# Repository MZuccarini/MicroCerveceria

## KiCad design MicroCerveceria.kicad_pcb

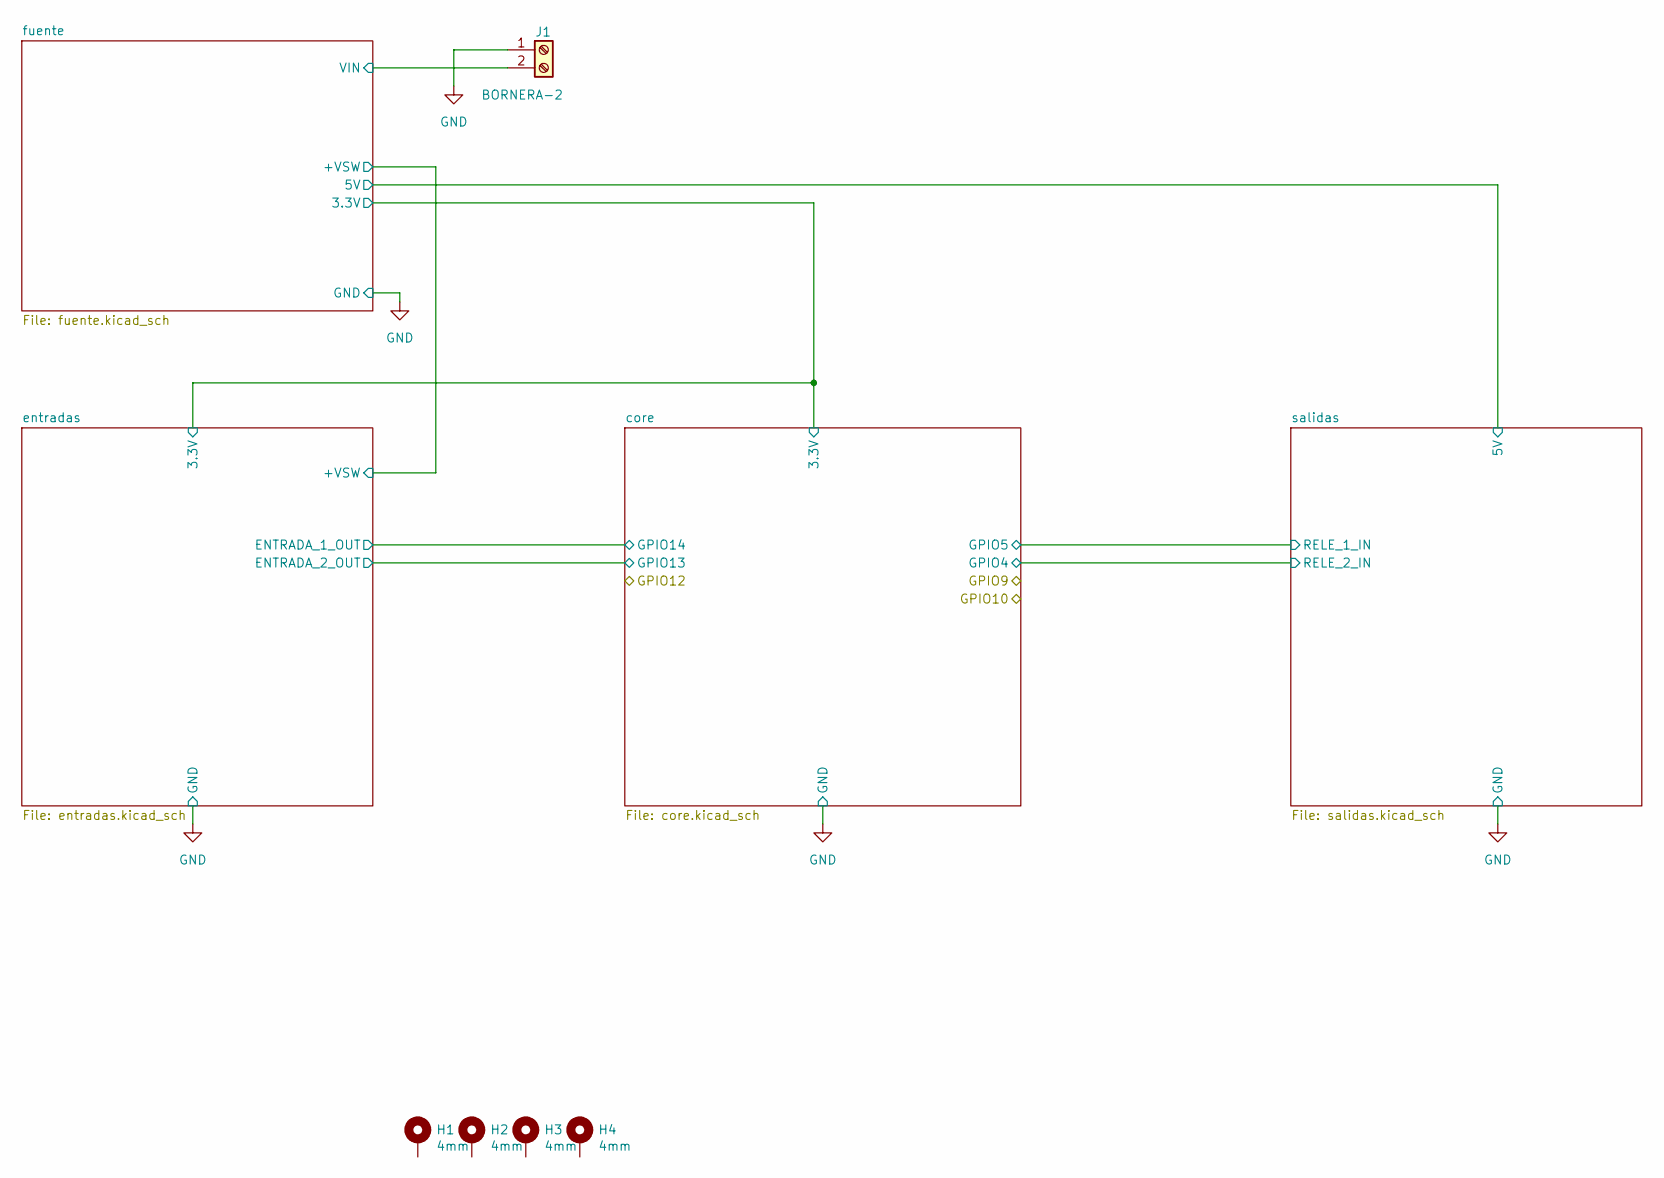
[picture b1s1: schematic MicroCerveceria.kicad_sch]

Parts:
H1, H2, H3, H4: 4mm; MountingHole_4mm_Pad
J1: BORNERA-2; TerminalBlock_Phoenix_MKDS-1,5-2-5.08_1x02_P5.08mm_Horizont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

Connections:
/fuente/VIN: J1.2; also elsewhere on the board
GND: J1.1; also elsewhere on the board

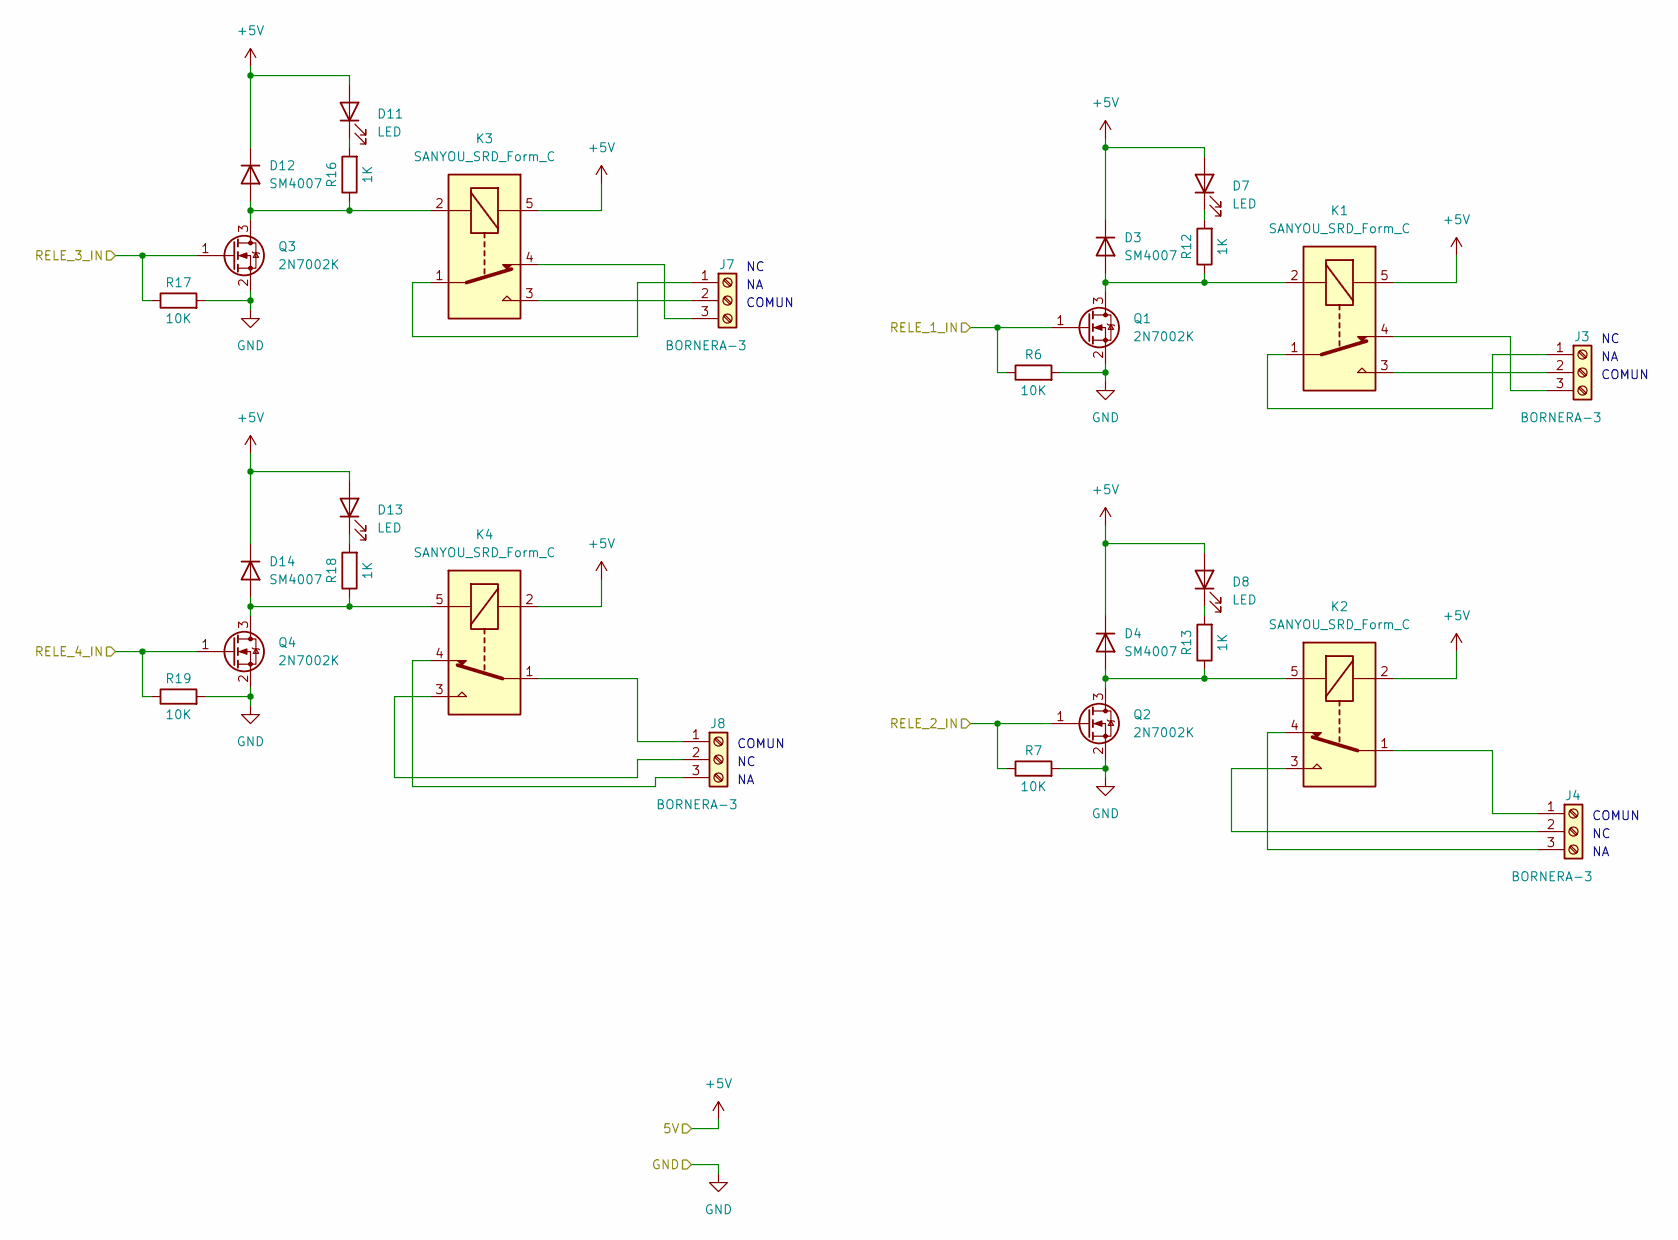
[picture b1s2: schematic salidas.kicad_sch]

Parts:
D3, D4, D12, D14: SM4007; D_SMA_Handsoldering
D7, D8, D11, D13: LED; LED_0805_2012Metric_Pad1.15x1.40mm_HandSolder
J3, J4, J7, J8: BORNERA-3; TerminalBlock_Phoenix_MKDS-1,5-3-5.08_1x03_P5.08mm_Horizont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
K1, K2, K3, K4: SANYOU_SRD_Form_C; Relay_SPDT_SANYOU_SRD_Series_Form_C
Q1, Q2, Q3, Q4: 2N7002K; SOT-23_Handsoldering
R6, R7, R17, R19: 10K; R_0805_2012Metric_Pad1.20x1.40mm_HandSolder
R12, R13, R16, R18: 1K; R_0805_2012Metric_Pad1.20x1.40mm_HandSolder

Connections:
+5V: D3.1 (K), D4.1 (K), D7.2 (A), D8.2 (A), D11.2 (A), D12.1 (K), D13.2 (A), D14.1 (K), K1.5, K2.2, K3.5, K4.2; also elsewhere on the board
/core/GPIO4: Q3.1 (G), R17.1; also elsewhere on the board
/core/GPIO5: Q4.1 (G), R19.1; also elsewhere on the board
/core/GPIO9: Q1.1 (G), R6.1; also elsewhere on the board
/core/GPIO10: Q2.1 (G), R7.1; also elsewhere on the board
GND: Q1.2 (S), Q2.2 (S), Q3.2 (S), Q4.2 (S), R6.2, R7.2, R17.2, R19.2; also elsewhere on the board
unnamed: D3.2 (A), K1.2, Q1.3 (D), R12.1
unnamed: D4.2 (A), K2.5, Q2.3 (D), R13.1
unnamed: D7.1 (K), R12.2
unnamed: D8.1 (K), R13.2
unnamed: D11.1 (K), R16.2
unnamed: D12.2 (A), K3.2, Q3.3 (D), R16.1
unnamed: D13.1 (K), R18.2
unnamed: D14.2 (A), K4.5, Q4.3 (D), R18.1
unnamed: J3.1, K1.1
unnamed: J3.2, K1.3
unnamed: J3.3, K1.4
unnamed: J4.1, K2.1
unnamed: J4.2, K2.3
unnamed: J4.3, K2.4
unnamed: J7.1, K3.1
unnamed: J7.2, K3.3
unnamed: J7.3, K3.4
unnamed: J8.1, K4.1
unnamed: J8.2, K4.3
unnamed: J8.3, K4.4

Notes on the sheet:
COMUN

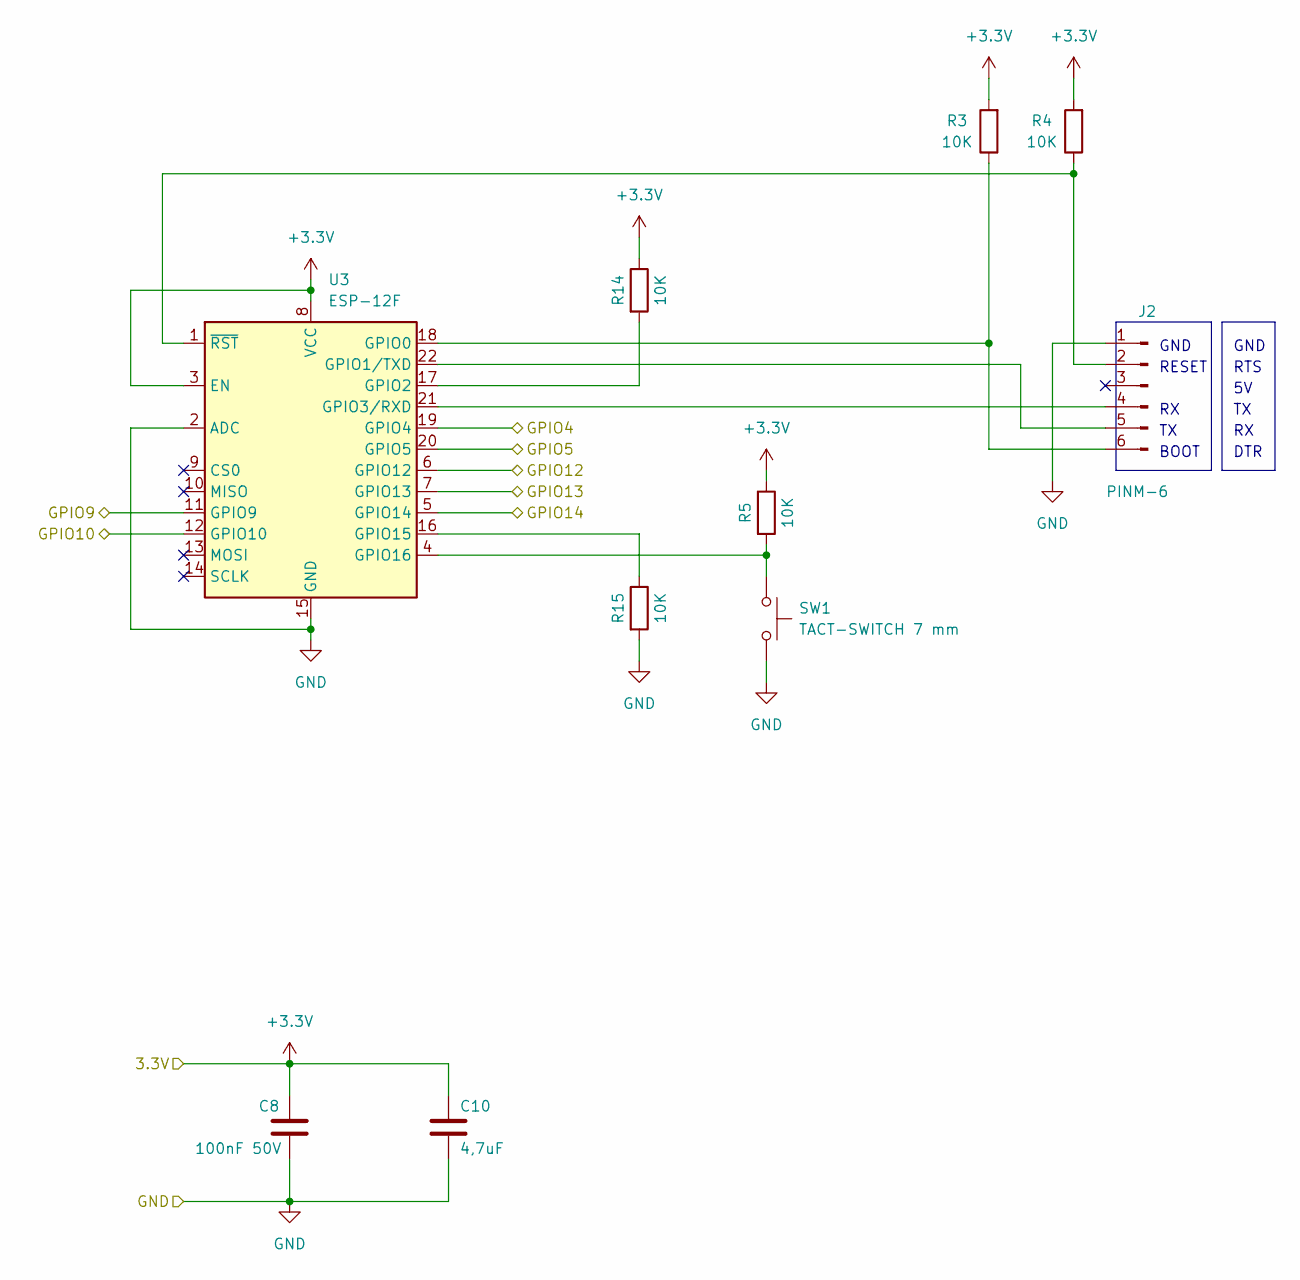
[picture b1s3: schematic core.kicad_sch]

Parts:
C8: 100nF 50V; C_0805_2012Metric_Pad1.18x1.45mm_HandSolder; DigiKey 1276-1007-2-ND
C10: 4,7uF; C_0805_2012Metric_Pad1.18x1.45mm_HandSolder
J2: PINM-6; PinHeader_1x06_P2.54mm_Vertical
R3, R4, R5, R14, R15: 10K; R_0805_2012Metric_Pad1.20x1.40mm_HandSolder
SW1: TACT-SWITCH 7 mm; SW_Tactile_SPST_Angled_PTS645Vx39-2LFS
U3: ESP-12F; ESP-12E

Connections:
+3V3: C8.1, C10.1, R3.2, R4.2, R5.1, R14.1, U3.3 (EN), U3.8 (VCC); also elsewhere on the board
/core/GPIO4: U3.19 (GPIO4); also elsewhere on the board
/core/GPIO5: U3.20 (GPIO5); also elsewhere on the board
/core/GPIO9: U3.11 (GPIO9); also elsewhere on the board
/core/GPIO10: U3.12 (GPIO10); also elsewhere on the board
/core/GPIO12: U3.6 (GPIO12); also elsewhere on the board
/core/GPIO13: U3.7 (GPIO13); also elsewhere on the board
/core/GPIO14: U3.5 (GPIO14); also elsewhere on the board
GND: C8.2, C10.2, J2.1, R15.2, SW1.1, U3.2 (ADC), U3.15 (GND); also elsewhere on the board
unnamed: J2.2, R4.1, U3.1 (~RST)
unnamed: J2.4, U3.21 (GPIO3/RXD)
unnamed: J2.5, U3.22 (GPIO1/TXD)
unnamed: J2.6, R3.1, U3.18 (GPIO0)
unnamed: R14.2, U3.17 (GPIO2)
unnamed: R15.1, U3.16 (GPIO15)
unnamed: R5.2, SW1.2, U3.4 (GPIO16)

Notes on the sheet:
GND
BOOT
RESET
RTS
DTR

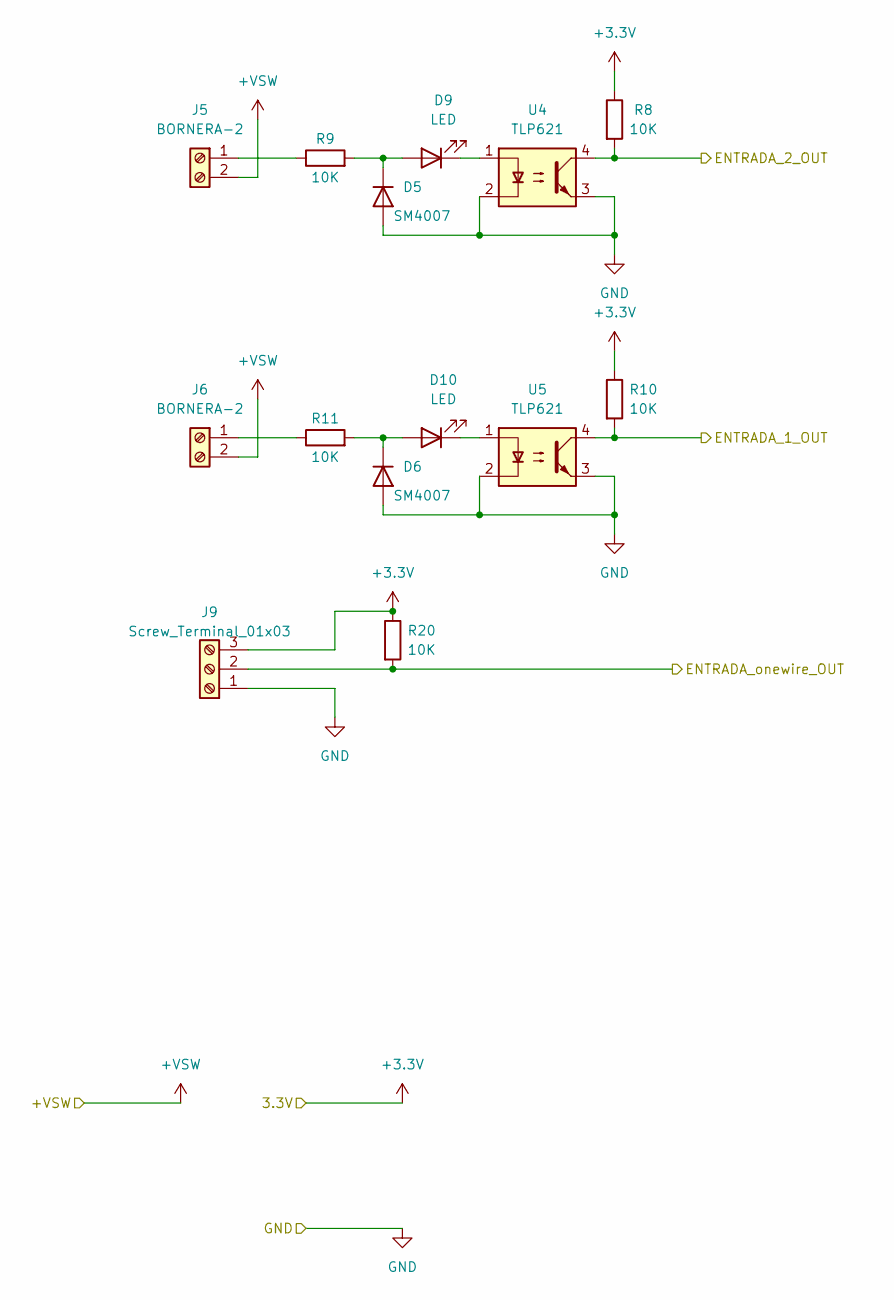
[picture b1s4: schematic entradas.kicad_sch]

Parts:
D5, D6: SM4007; D_SMA_Handsoldering
D9, D10: LED; LED_0805_2012Metric_Pad1.15x1.40mm_HandSolder
J5, J6: BORNERA-2; TerminalBlock_Phoenix_MKDS-1,5-2-5.08_1x02_P5.08mm_Horizont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
J9: Screw_Terminal_01x03; TerminalBlock_Phoenix_MKDS-1,5-3-5.08_1x03_P5.08mm_Horizont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
R8, R9, R10, R11, R20: 10K; R_0805_2012Metric_Pad1.20x1.40mm_HandSolder
U4, U5: TLP621; DIP-4_W7.62mm

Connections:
+3V3: J9.3, R8.1, R10.1, R20.1; also elsewhere on the board
+VSW: J5.2, J6.2; also elsewhere on the board
/core/GPIO12: J9.2, R20.2; also elsewhere on the board
/core/GPIO13: R8.2, U4.4; also elsewhere on the board
/core/GPIO14: R10.2, U5.4; also elsewhere on the board
GND: D5.2 (A), D6.2 (A), J9.1, U4.2, U4.3, U5.2, U5.3; also elsewhere on the board
unnamed: D5.1 (K), D9.2 (A), R9.2
unnamed: D9.1 (K), U4.1
unnamed: D6.1 (K), D10.2 (A), R11.2
unnamed: D10.1 (K), U5.1
unnamed: J5.1, R9.1
unnamed: J6.1, R11.1

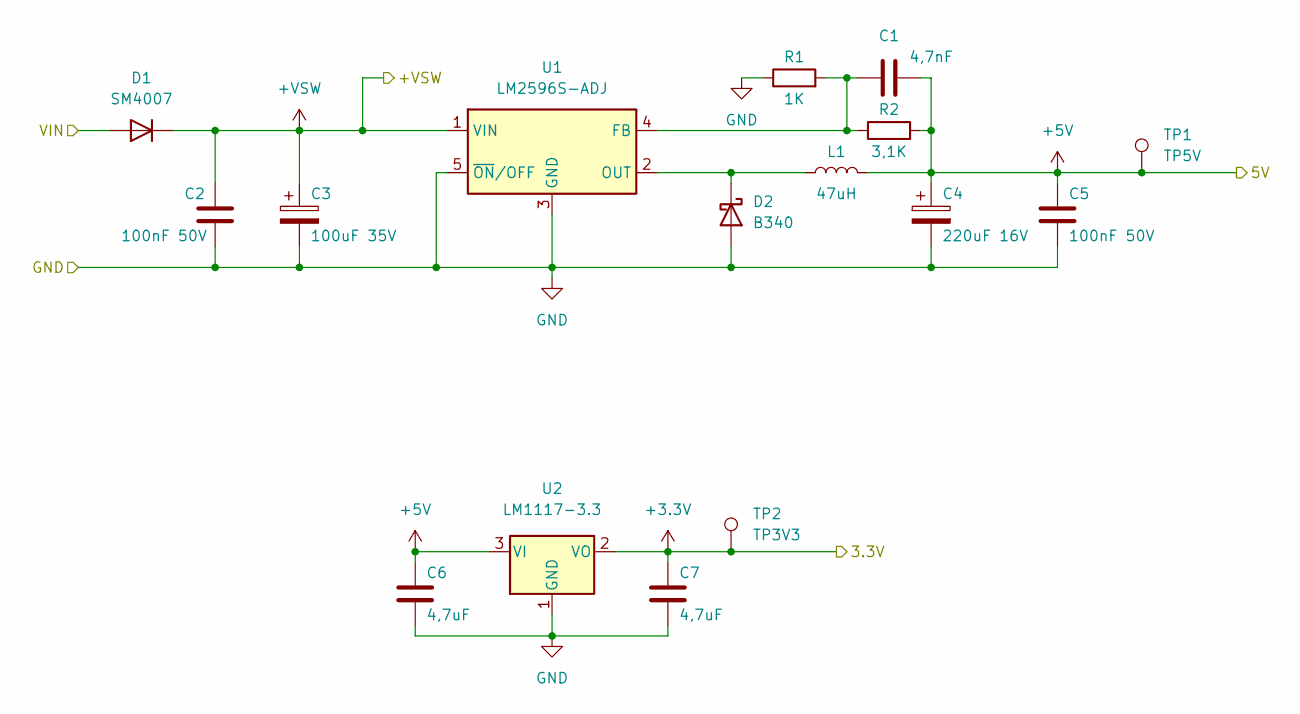
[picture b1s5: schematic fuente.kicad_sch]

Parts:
C1: 4,7nF; C_0805_2012Metric_Pad1.18x1.45mm_HandSolder
C2, C5: 100nF 50V; C_0805_2012Metric_Pad1.18x1.45mm_HandSolder; DigiKey 1276-1007-2-ND
C3: 100uF 35V; CP_Elec_6.3x7.7
C4: 220uF 16V; CP_Elec_6.3x7.7
C6, C7: 4,7uF; C_0805_2012Metric_Pad1.18x1.45mm_HandSolder
D1: SM4007; D_SMA_Handsoldering
D2: B340; D_SMC
L1: 47uH; L_Radial_D7.5mm_P5.00mm_Fastron_07P
R1: 1K; R_0805_2012Metric_Pad1.20x1.40mm_HandSolder
R2: 3,1K; R_0805_2012Metric_Pad1.20x1.40mm_HandSolder
TP1: TP5V; TestPoint_Loop_D2.50mm_Drill1.0mm
TP2: TP3V3; TestPoint_Loop_D2.50mm_Drill1.0mm
U1: LM2596S-ADJ; TO-263-5_TabPin3
U2: LM1117-3.3; SOT-223-3_TabPin2

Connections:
+3V3: C7.1, TP2.1, U2.2 (VO); also elsewhere on the board
+5V: C1.2, C4.1, C5.1, C6.1, L1.2, R2.2, TP1.1, U2.3 (VI); also elsewhere on the board
+VSW: C2.1, C3.1, D1.1 (K), U1.1 (VIN); also elsewhere on the board
/fuente/VIN: D1.2 (A); also elsewhere on the board
GND: C2.2, C3.2, C4.2, C5.2, C6.2, C7.2, D2.2 (A), R1.1, U1.3 (GND), U1.5 (~ON/OFF), U2.1 (GND); also elsewhere on the board
unnamed: D2.1 (K), L1.1, U1.2 (OUT)
unnamed: C1.1, R1.2, R2.1, U1.4 (FB)

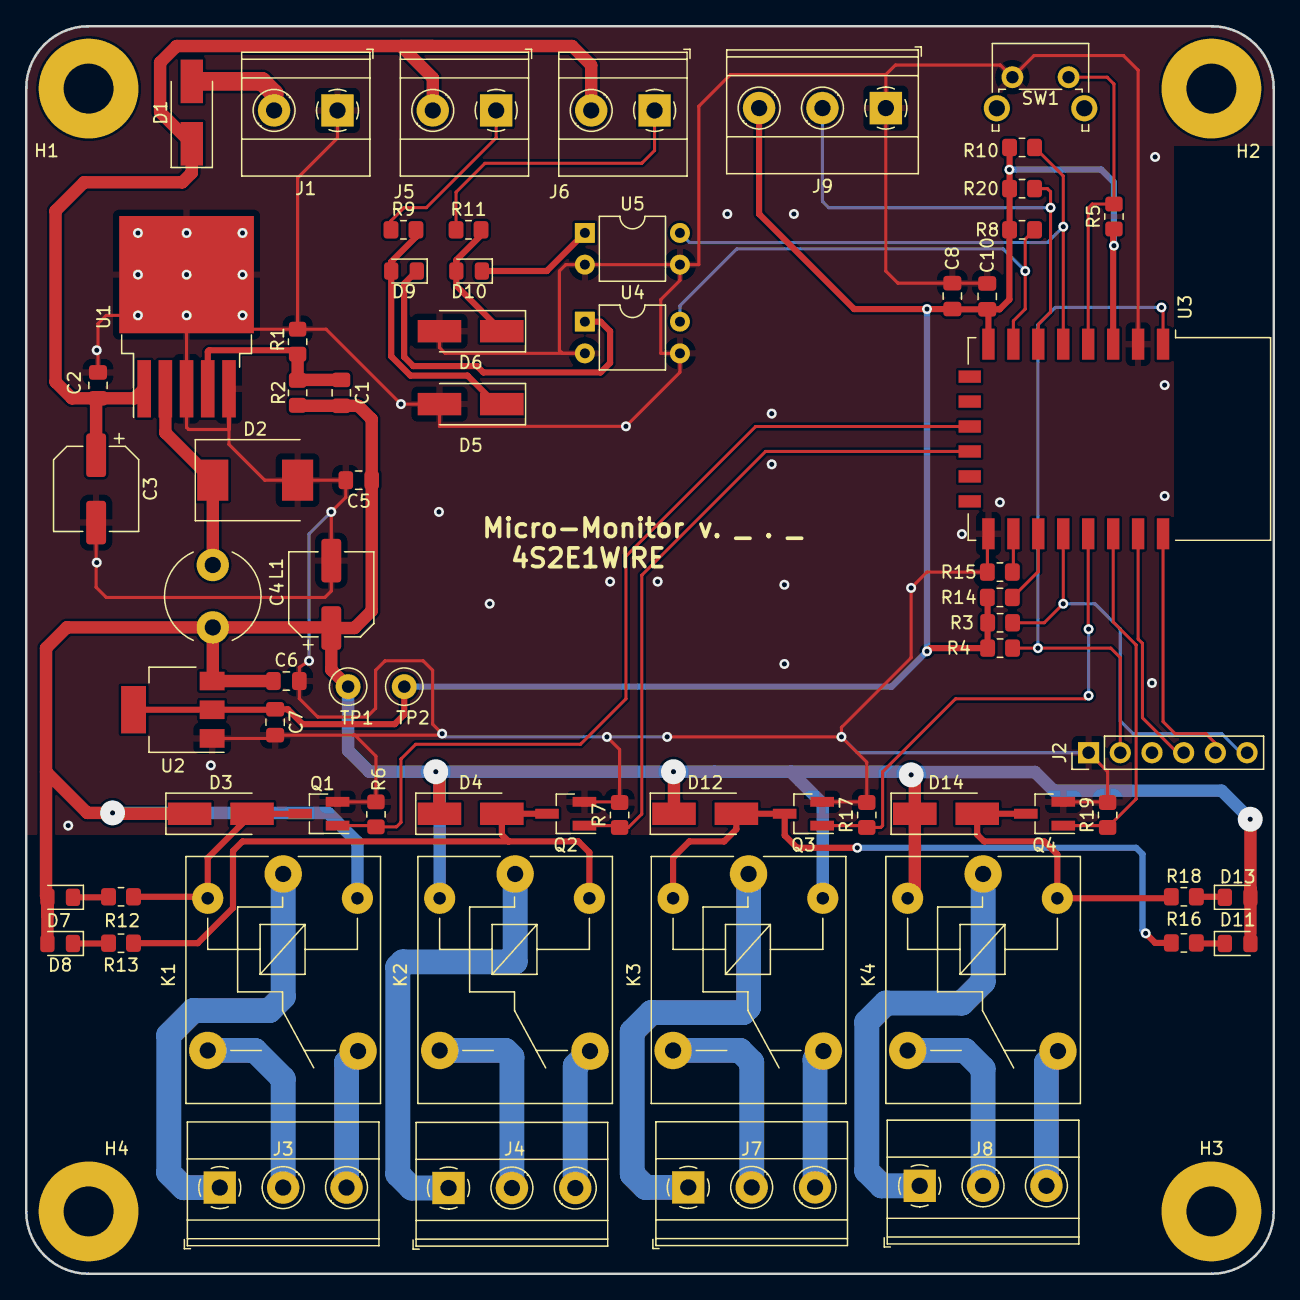
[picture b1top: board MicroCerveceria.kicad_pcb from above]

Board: 2 copper layers, 100.0 x 100.0 mm, 73 parts (0 on the bottom side), 47 nets.

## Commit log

2025-03-13 Se agrega el proyecto
2025-03-16 Finaliza PCB
2025-03-17 Creacion gerber y listado de componentes
